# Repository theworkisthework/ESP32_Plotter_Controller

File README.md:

# ESP32 Plotter Controller PCB
 
Released under an MIT licence, no warranty implied or given, use at own risk etc etc.

This is a two axis stepper controller based on the ESP32 and TMC2130 stepper drivers. It is intended to be used with drawing machines and plotters.

Firmware https://github.com/theworkisthework/Grbl_Esp32 (This is a Fork of Grbl_Esp32, if its out of date, you probably only need the config file from this fork). Tested with standard and corexy kinematics and a solenoid/relay for the spindle.

Revision B (aka 'Emerald Dingo') embeds an ESP32 module on the board along with comms and USB C connector. The peripheral connectors are all JST PH2.0 connectors. Also added E-Stop connector (J18).

[Schematic]( https://github.com/theworkisthework/ESP32_Plotter_Controller/blob/main/ESP32_Plotter_Controller_Schematic_RevB1.pdf )

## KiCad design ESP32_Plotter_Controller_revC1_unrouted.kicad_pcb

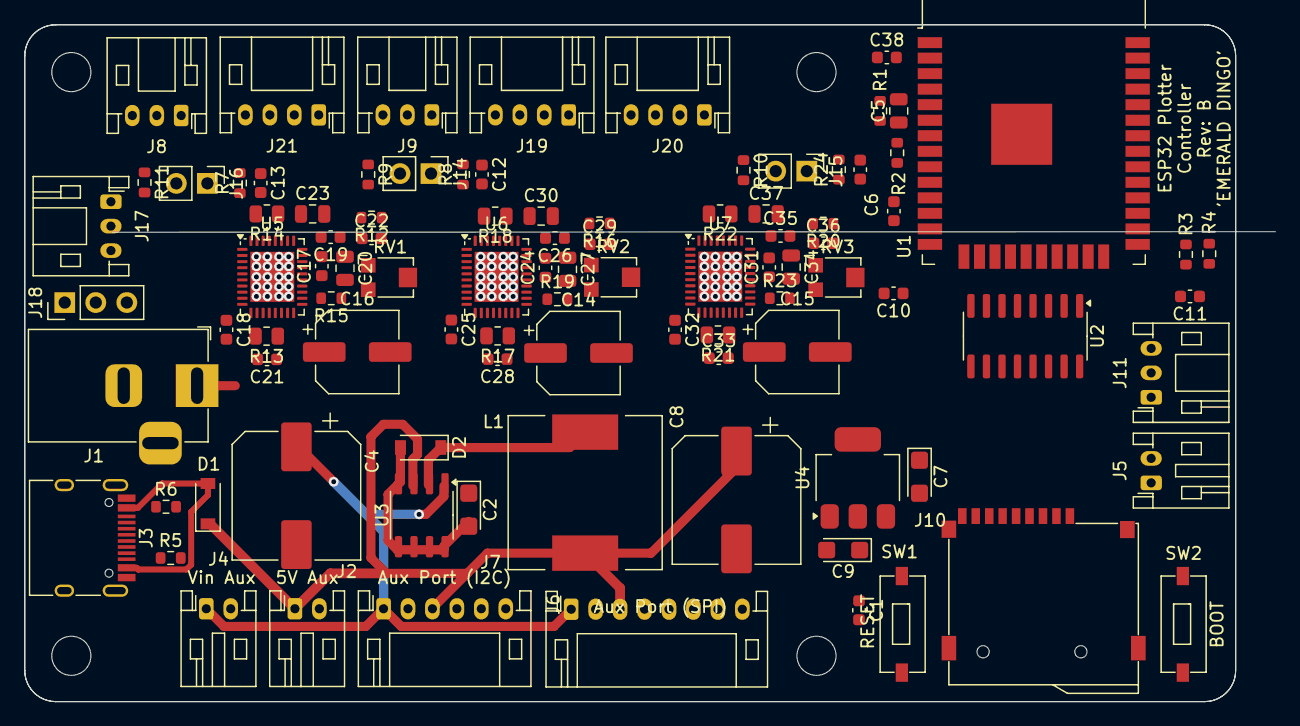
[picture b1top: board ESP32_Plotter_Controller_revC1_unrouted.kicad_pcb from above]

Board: 2 copper layers, 102.3 x 55.4 mm, 96 parts (0 on the bottom side), 83 nets.

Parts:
C1, C3, C6, C10, C11, C12, C13, C38: 100nF; C_0603_1608Metric
C2, C7, C9: 22uF 10v; CP_EIA-3216-18_Kemet-A
C4: 470uF 35v; CP_Elec_10x10
C5: 1uF; C_0805_2012Metric
C8: 220uF 50v; CP_Elec_10x10
C14, C15, C16: 47uF 35V; CP_Elec_6.3x5.7
C17, C24, C31: 22n; C_0603_1608Metric
C18, C19, C21, C25, C26, C28, C32, C33, C35: 100n; C_0603_1608Metric
C20, C27, C34: 4.7u; C_0805_2012Metric
C22, C29, C36: 470n; C_0603_1608Metric
C23, C30, C37: 10u; C_0805_2012Metric
D1, D2: B5819W; D_SOD-123
J1: Power; BarrelJack_Horizontal
J2: 5V Aux; JST_PH_S2B-PH-K_1x02_P2.00mm_Horizontal
J3: USB_C_Receptacle_USB2.0; USB_C_Receptacle_HRO_TYPE-C-31-M-12
J4: Vin Aux; JST_PH_S2B-PH-K_1x02_P2.00mm_Horizontal
J5: E-Stop; JST_PH_S2B-PH-K_1x02_P2.00mm_Horizontal
J6: Aux Port (SPI); JST_PH_S8B-PH-K_1x08_P2.00mm_Horizontal
J7: Aux Port (I2C); JST_PH_S6B-PH-K_1x06_P2.00mm_Horizontal
J8: X Limit Switch; JST_PH_S3B-PH-K_1x03_P2.00mm_Horizontal
J9: Y Limit Switch; JST_PH_S3B-PH-K_1x03_P2.00mm_Horizontal
J10: Micro_SD_Card_TF-01A; HK-TF01A
J11: Z Limit Switch; JST_PH_S3B-PH-K_1x03_P2.00mm_Horizontal
J14: Y Limit; PinHeader_1x02_P2.54mm_Vertical
J15: Z Limit; PinHeader_1x02_P2.54mm_Vertical
J16: X Limit; PinHeader_1x02_P2.54mm_Vertical
J17: Pen Lift; JST_PH_S3B-PH-K_1x03_P2.00mm_Horizontal
J18: Vselect; PinHeader_1x03_P2.54mm_Vertical
J19: Y Motor; JST_PH_S4B-PH-K_1x04_P2.00mm_Horizontal
J20: Z Motor; JST_PH_S4B-PH-K_1x04_P2.00mm_Horizontal
J21: X Motor; JST_PH_S4B-PH-K_1x04_P2.00mm_Horizontal
L1: 68uH; L_12x12mm_H6mm
R1, R3: 5.1k; R_0603_1608Metric
R2, R4, R5, R6, R9, R10, R11: 10k; R_0603_1608Metric
R7, R8, R24: 100; R_0603_1608Metric
R12, R16, R20: 20k; R_0603_1608Metric
R13, R14, R17, R18, R21, R22: 0.11R; R_0805_2012Metric
R15, R19, R23: 2.2R; R_0603_1608Metric
RV1, RV2, RV3: 20k; Potentiometer_Bourns_TC33X_Vertical
SW1: RESET; K2-1107ST
SW2: BOOT; K2-1107ST
U1: ESP32-WROOM-32D; ESP32-WROOM-32
U2: CH340C; SOIC-16_3.9x9.9mm_P1.27mm
U3: XL1509; SO-8_3.9x4.9mm_P1.27mm
U4: AMS1117-3.3; SOT-223-3_TabPin2
U5, U6, U7: TMC2130-LA; QFN-36-1EP_5x6mm_P0.5mm_EP3.6x4.1mm

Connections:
+3.3V: C2.1, C3.1, C6.1, C9.1, C11.1, J6.2, J7.2, J9.1, J10.4 (VDD), J11.1, R2.2, R4.1, R5.1, R6.1, R9.1, R10.1, R11.1, U1.2 (3v3), U2.4 (V3), U2.16 (VCC), U4.2 (VO)
+5V: C7.1, C8.1, D1.1 (K), J2.1, J6.3, J7.3, J18.1, L1.2, U3.3 (Feedback), U4.3 (VI)
/CS_AUX: J6.8, U1.26 (IO4)
/CS_SD: J10.2 (DAT3/CD), U1.29 (IO5)
/CS_X: U1.28 (IO17), U5.2 (~CS_CFG3)
/CS_Y: U1.27 (IO16), U6.2 (~CS_CFG3)
/CS_Z: U1.23 (IO15), U7.2 (~CS_CFG3)
/D+: J3.A6 (D+), J3.B6 (D+), U2.5 (UD+)
/D-: J3.A7 (D-), J3.B7 (D-), U2.6 (UD-)
/EN: C1.2, R2.1, SW1.2, U1.3 (EN)
/ESP32_RX: U1.34 (RXD0), U2.2 (TXD)
/ESP32_TX: U1.35 (TXD0), U2.3 (RXD)
/IO0: C10.1, J5.1, R4.2, SW2.2, U1.25 (IO0)
/MISO: J6.6, J10.7 (DAT0), U1.31 (IO19), U5.5 (SDO_CFG0), U6.5 (SDO_CFG0), U7.5 (SDO_CFG0)
/MOSI: J6.5, J10.3 (CMD), U1.37 (IO23), U5.4 (SDI_CFG1), U6.4 (SDI_CFG1), U7.4 (SDI_CFG1)
/PEN_LIFT: J17.1, U1.12 (IO27)
/SCK: J6.7, J10.5 (CLK), U1.30 (IO18), U5.3 (SCK_CFG2), U6.3 (SCK_CFG2), U7.3 (SCK_CFG2)
/SCL: J7.5, R6.2, U1.36 (IO22)
/SDA: J7.6, R5.2, U1.33 (IO21)
/StepEn: U1.24 (IO2), U5.22 (~DRV_EN_CFG6), U6.22 (~DRV_EN_CFG6), U7.22 (~DRV_EN_CFG6)
/TMC2130_EMBD_1/5VOUT: C20.1, R15.1, U5.25 (5VOUT)
/TMC2130_EMBD_1/A1: J21.2, U5.34 (OA1)
/TMC2130_EMBD_1/A2: J21.1, U5.32 (OA2)
/TMC2130_EMBD_1/B1: J21.3, U5.13 (OB1)
/TMC2130_EMBD_1/B2: J21.4, U5.15 (OB2)
/TMC2130_EMBD_1/DIAG1: J16.2, R11.2, U5.21 (DIAG1)
/TMC2130_EMBD_1/VCC_INT: C22.1, R12.2, R15.2, U5.19 (DCIN_CFG5), U5.26 (VCC)
/TMC2130_EMBD_1/VCP: C19.2, U5.29 (VCP)
/TMC2130_EMBD_1/V_IO: C18.1, U5.8 (VCC_IO)
/TMC2130_EMBD_2/5VOUT: C27.1, R19.1, U6.25 (5VOUT)
/TMC2130_EMBD_2/A1: J19.2, U6.34 (OA1)
/TMC2130_EMBD_2/A2: J19.1, U6.32 (OA2)
/TMC2130_EMBD_2/B1: J19.3, U6.13 (OB1)
/TMC2130_EMBD_2/B2: J19.4, U6.15 (OB2)
/TMC2130_EMBD_2/DIAG1: J14.2, R9.2, U6.21 (DIAG1)
/TMC2130_EMBD_2/VCC_INT: C29.1, R16.2, R19.2, U6.19 (DCIN_CFG5), U6.26 (VCC)
/TMC2130_EMBD_2/VCP: C26.2, U6.29 (VCP)
/TMC2130_EMBD_2/V_IO: C25.1, U6.8 (VCC_IO)
/TMC2130_EMBD_3/5VOUT: C34.1, R23.1, U7.25 (5VOUT)
/TMC2130_EMBD_3/A1: J20.2, U7.34 (OA1)
/TMC2130_EMBD_3/A2: J20.1, U7.32 (OA2)
/TMC2130_EMBD_3/B1: J20.3, U7.13 (OB1)
/TMC2130_EMBD_3/B2: J20.4, U7.15 (OB2)
/TMC2130_EMBD_3/DIAG1: J15.2, R10.2, U7.21 (DIAG1)
/TMC2130_EMBD_3/VCC_INT: C36.1, R20.2, R23.2, U7.19 (DCIN_CFG5), U7.26 (VCC)
/TMC2130_EMBD_3/VCP: C33.2, U7.29 (VCP)
/TMC2130_EMBD_3/V_IO: C32.1, U7.8 (VCC_IO)
/Vin: C4.1, C5.1, C14.1, C15.1, C16.1, C19.1, C21.1, C23.1, C26.1, C28.1, C30.1, C33.1, C35.1, C37.1, J1.1, J4.1, J6.1, J7.1, J18.3, U3.1 (Vin), U5.16 (VS), U5.30 (VSA), U5.31 (VS), U6.16 (VS), U6.30 (VSA), U6.31 (VS), U7.16 (VS), U7.30 (VSA), U7.31 (VS)
/X_Dir: U1.11 (IO26), U5.7 (DIR)
/X_Limit: C13.1, J16.1, R7.1, U1.6 (IO34)
/X_Step: U1.10 (IO25), U5.6 (STEP)
/Y_Dir: U1.9 (IO33), U6.7 (DIR)
/Y_Limit: C12.1, J14.1, R8.1, U1.7 (IO35)
/Y_Step: U1.8 (IO32), U6.6 (STEP)
/Z_Limit: C38.1, J15.1, R24.1, U1.14 (IO12)
/Z_Step: U1.13 (IO14), U7.6 (STEP)
GND: C1.1, C2.2, C3.2, C4.2, C5.2, C6.2, C7.2, C8.2, C9.2, C10.2, C11.2, C12.2, C13.2, C14.2, C15.2, C16.2, C18.2, C20.2, C21.2, C22.2, C23.2, C25.2, C27.2, C28.2, C29.2, C30.2, C32.2, C34.2, C35.2, C36.2, C37.2, C38.2, D2.2 (A), J1.2, J2.2, J3.A1 (GND), J3.A12 (GND), J3.B1 (GND), J3.B12 (GND), J4.2, J5.2, J6.4, J7.4, J8.3, J9.3, J10.6 (VSS), J10.10 (Can), J10.11 (Can), J10.12 (Can), J10.13 (Can), J11.3, J17.3, R1.2, R3.2, R13.2, R14.2, R17.2, R18.2, R21.2, R22.2, RV1.3, RV2.3, RV3.3, SW1.1, SW2.1, U1.1 (GND), U1.15 (GND), U1.38 (GND), U1.39 (GND), U2.1 (GND), U3.4 (~EN), U3.5 (GND), U3.6 (GND), U3.7 (GND), U3.8 (GND), U4.1 (GND), U5.1 (CLK), U5.12 (GNDP), U5.17 (DCO), U5.18 (DCEN_CFG4), U5.24 (GNDA), U5.35 (GNDP), U5.36 (TST_MODE), U5.37 (EP), U6.1 (CLK), U6.12 (GNDP), U6.17 (DCO), U6.18 (DCEN_CFG4), U6.24 (GNDA), U6.35 (GNDP), U6.36 (TST_MODE), U6.37 (EP), U7.1 (CLK), U7.12 (GNDP), U7.17 (DCO), U7.18 (DCEN_CFG4), U7.24 (GNDA), U7.35 (GNDP), U7.36 (TST_MODE), U7.37 (EP)
unnamed: D1.2 (A), J3.A4 (VBUS), J3.A9 (VBUS), J3.B4 (VBUS), J3.B9 (VBUS)
unnamed: D2.1 (K), L1.1, U3.2 (Vout)
unnamed: J3.A5 (CC1), R3.1
unnamed: J3.B5 (CC2), R1.1
unnamed: J8.2, R7.2
unnamed: J9.2, R8.2
unnamed: J11.2, R24.2
unnamed: J17.2, J18.2
unnamed: R12.1, RV1.2
unnamed: R16.1, RV2.2
unnamed: R20.1, RV3.2
unnamed: RV1.1, U5.23 (AIN_IREF)
unnamed: R14.1, U5.33 (BRA)
unnamed: R13.1, U5.14 (BRB)
unnamed: C17.2, U5.28 (CPI)
unnamed: C17.1, U5.27 (CPO)
unnamed: RV2.1, U6.23 (AIN_IREF)
unnamed: R18.1, U6.33 (BRA)
unnamed: R17.1, U6.14 (BRB)
unnamed: C24.2, U6.28 (CPI)
unnamed: C24.1, U6.27 (CPO)
unnamed: RV3.1, U7.23 (AIN_IREF)
unnamed: R22.1, U7.33 (BRA)
unnamed: R21.1, U7.14 (BRB)
unnamed: C31.2, U7.28 (CPI)
unnamed: C31.1, U7.27 (CPO)

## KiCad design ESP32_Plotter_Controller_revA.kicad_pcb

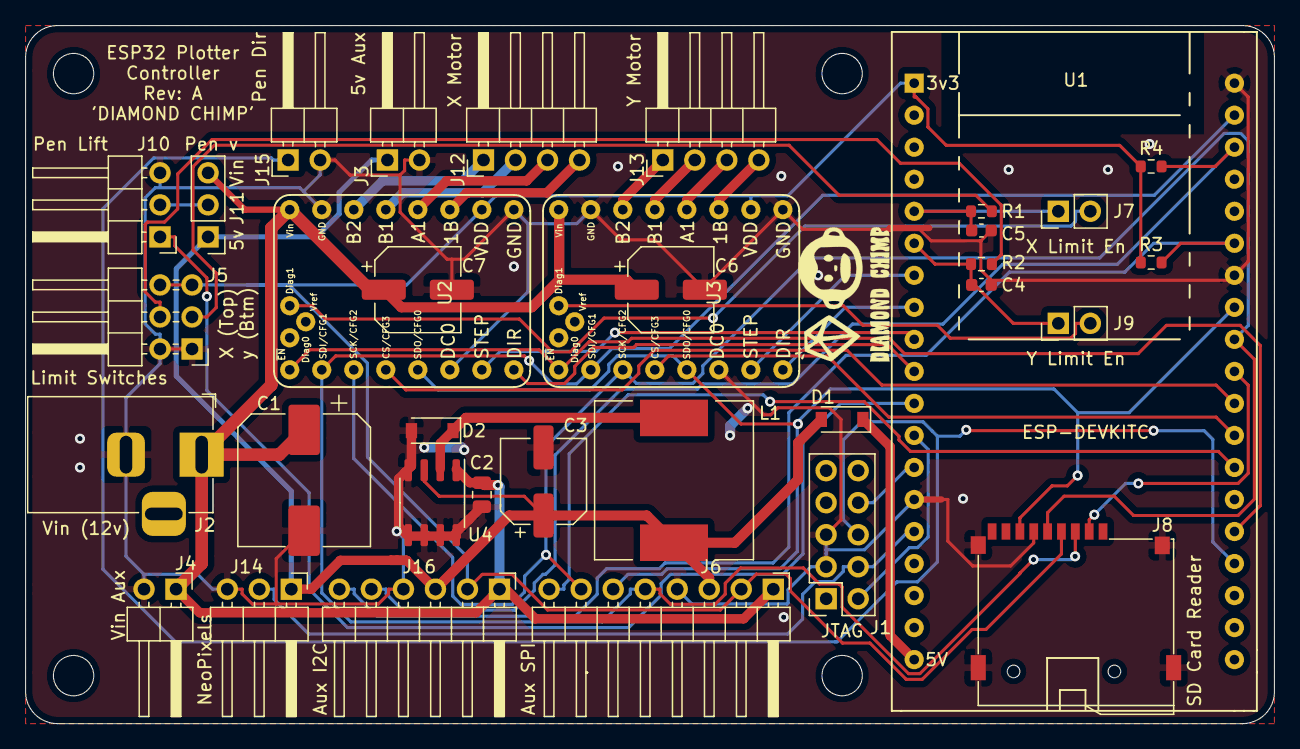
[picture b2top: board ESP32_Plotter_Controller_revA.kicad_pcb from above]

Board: 2 copper layers, 99.1 x 55.4 mm, 38 parts (0 on the bottom side), 40 nets.

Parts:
C1: 470uF 35v; CP_Elec_10x10
C2: 1uF; C_0805_2012Metric
C3: 180uF 35v; CP_Elec_6.3x7.7
C4, C5: 100nF; C_0603_1608Metric
C6, C7: 47uF 35V; CP_Elec_6.3x5.7
D1, D2: B5819W; D_SOD-123
H1, H2, H3, H4: MountingHole_3.2mm_M3
J1: ARM JTAG 10pin; PinSocket_2x05_P2.54mm_Vertical
J2: Power; BarrelJack_Horizontal
J3: 5V Aux; PinHeader_1x02_P2.54mm_Horizontal
J4: Vin Aux; PinHeader_1x02_P2.54mm_Horizontal
J5: Limit Switches; PinHeader_2x03_P2.54mm_Horizontal
J6: Aux Port (SPI); PinHeader_1x08_P2.54mm_Horizontal
J7: X Limit; PinHeader_1x02_P2.54mm_Vertical
J8: Micro_SD_Card_TF-01A; HK-TF01A
J9: Y Limit; PinHeader_1x02_P2.54mm_Vertical
J10: Pen Lift; PinHeader_1x03_P2.54mm_Horizontal
J11: Vselect; PinHeader_1x03_P2.54mm_Vertical
J12: X Motor; PinHeader_1x04_P2.54mm_Horizontal
J13: Y Motor; PinHeader_1x04_P2.54mm_Horizontal
J14: Neo Pixel LEDs; PinHeader_1x03_P2.54mm_Horizontal
J15: Pen Direction; PinHeader_1x02_P2.54mm_Horizontal
J16: Aux Port (I2C); PinHeader_1x06_P2.54mm_Horizontal
L1: 68uH; L_12x12mm_H6mm
R1, R2: 100; R_0603_1608Metric
R3, R4: 10K; R_0603_1608Metric
U1: ESP-DEVKITC; DEVKITC
U2, U3: TMC2130; StepstickTMCv2
U4: XL1509; SO-8_3.9x4.9mm_P1.27mm

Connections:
+3V3: J5.5, J5.6, J6.2, J8.4, J16.2, R3.1, R4.1, U1.1, U2.10, U3.10
+5V: C3.1, D1.2, J3.1, J6.3, J11.1, J14.1, J16.3, L1.2, U4.3
/CS_AUX: J6.8, U1.26
/CS_SD: J8.2, U1.29
/CS_X: U1.28, U2.4
/CS_Y: U1.27, U3.4
/JTAG_TDI: J1.8, U1.13
/JTAG_TMS: J1.2, U1.12
/MISO: J6.6, J8.7, U1.31, U2.5, U3.5
/MOSI: J6.5, J8.3, U1.37, U2.2, U3.2
/NEO_PIXELS_JTAG_TCK: J1.4, J14.2, U1.15
/PEN_DIR_JTAG_TDO: J1.6, J15.1, U1.23
/PEN_LIFT: J10.1, U1.11
/SCK: J6.7, J8.5, U1.30, U2.3, U3.3
/SCL: J16.5, R4.2, U1.36
/SDA: J16.6, R3.2, U1.33
/StepEn: U1.24, U2.1, U3.1
/Vin: C1.1, C2.1, C6.1, C7.1, J2.1, J4.1, J6.1, J11.3, J16.1, U2.16, U3.16, U4.1
/X_Dir: U1.10, U2.8
/X_Limit: C5.1, J7.1, R1.1, U1.5
/X_Step: U1.9, U2.7
/Y_Dir: U1.8, U3.8
/Y_Limit: C4.1, J9.1, R2.1, U1.6
/Y_Step: U1.7, U3.7
GND: C1.2, C2.2, C3.2, C4.2, C5.2, C6.2, C7.2, D2.2, J1.3, J1.5, J2.2, J3.2, J4.2, J5.1, J5.2, J6.4, J8.6, J8.10, J8.11, J8.12, J8.13, J10.3, J14.3, J15.2, J16.4, U1.14, U1.32, U1.38, U2.6, U2.9, U2.15, U3.6, U3.9, U3.15, U4.4, U4.5, U4.6, U4.7, U4.8
unnamed: D1.1, U1.19
unnamed: D2.1, L1.1, U4.2
unnamed: J5.3, R1.2
unnamed: J5.4, R2.2
unnamed: J7.2, U2.18
unnamed: J9.2, U3.18
unnamed: J10.2, J11.2
unnamed: J12.1, U2.14
unnamed: J12.2, U2.13
unnamed: J12.3, U2.12
unnamed: J12.4, U2.11
unnamed: J13.1, U3.14
unnamed: J13.2, U3.13
unnamed: J13.3, U3.12
unnamed: J13.4, U3.11

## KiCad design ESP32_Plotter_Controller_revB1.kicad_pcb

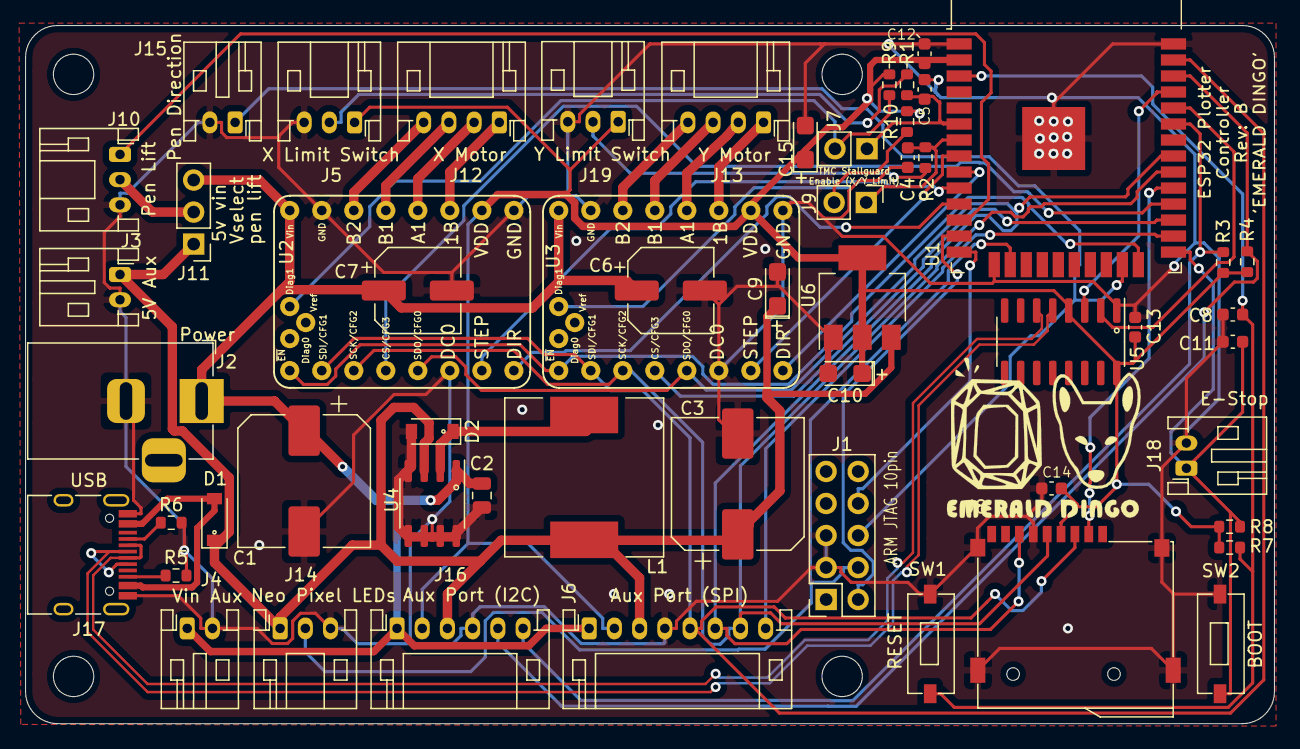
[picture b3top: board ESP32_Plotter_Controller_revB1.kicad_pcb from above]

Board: 2 copper layers, 99.1 x 55.4 mm, 61 parts (1 on the bottom side), 48 nets.

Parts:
C1: 470uF 35v; CP_Elec_10x10
C2: 1uF; C_0805_2012Metric
C3: 220uF 50v; CP_Elec_10x10
C4, C5, C8, C11, C12, C13, C14: 100nF; C_0603_1608Metric
C6, C7: 47uF 35V; CP_Elec_6.3x5.7
C9, C10, C15: 22uF 10v; CP_EIA-3216-18_Kemet-A
D1, D2: B5819W; D_SOD-123
G1: LOGO; emerald_dingo_400
G2: LOGO; emerald_dingo_150
H1, H2, H3, H4: MountingHole_3.2mm_M3
J1: ARM JTAG 10pin; PinSocket_2x05_P2.54mm_Vertical
J2: Power; BarrelJack_Horizontal
J3: 5V Aux; JST_PH_S2B-PH-K_1x02_P2.00mm_Horizontal
J4: Vin Aux; JST_PH_S2B-PH-K_1x02_P2.00mm_Horizontal
J5: X Limit Switch; JST_PH_S3B-PH-K_1x03_P2.00mm_Horizontal
J6: Aux Port (SPI); JST_PH_S8B-PH-K_1x08_P2.00mm_Horizontal
J7: X Limit; PinHeader_1x02_P2.54mm_Vertical
J8: Micro_SD_Card_TF-01A; HK-TF01A
J9: Y Limit; PinHeader_1x02_P2.54mm_Vertical
J10: Pen Lift; JST_PH_S3B-PH-K_1x03_P2.00mm_Horizontal
J11: Vselect; PinHeader_1x03_P2.54mm_Vertical
J12: X Motor; JST_PH_S4B-PH-K_1x04_P2.00mm_Horizontal
J13: Y Motor; JST_PH_S4B-PH-K_1x04_P2.00mm_Horizontal
J14: Neo Pixel LEDs; JST_PH_S3B-PH-K_1x03_P2.00mm_Horizontal
J15: Pen Direction; JST_PH_S2B-PH-K_1x02_P2.00mm_Horizontal
J16: Aux Port (I2C); JST_PH_S6B-PH-K_1x06_P2.00mm_Horizontal
J17: USB_C_Receptacle_USB2.0; USB_C_Receptacle_HRO_TYPE-C-31-M-12
J18: E-Stop; JST_PH_S2B-PH-K_1x02_P2.00mm_Horizontal
J19: Y Limit Switch; JST_PH_S3B-PH-K_1x03_P2.00mm_Horizontal
L1: 68uH; L_12x12mm_H6mm
R1, R2: 100; R_0603_1608Metric
R3, R4, R7, R8, R9, R10: 10k; R_0603_1608Metric
R5, R6: 5.1k; R_0603_1608Metric
SW1: RESET; K2-1107ST
SW2: BOOT; K2-1107ST
U1: ESP32-WROOM-32D; ESP32-WROOM-32
U2, U3: TMC2130; StepstickTMCv2
U4: XL1509; SO-8_3.9x4.9mm_P1.27mm
U5: CH340C; SOIC-16_3.9x9.9mm_P1.27mm
U6: AMS1117-3.3; SOT-223-3_TabPin2

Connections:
+3V3: C10.1, C12.1, C13.1, C14.1, C15.1, J5.1, J6.2, J8.4, J16.2, J19.1, R3.1, R4.1, R7.2, R8.1, R9.1, R10.1, U1.2, U2.10, U3.10, U5.4, U5.16, U6.2
+5V: C3.1, C9.1, D1.1, J3.1, J6.3, J11.1, J14.1, J16.3, L1.2, U4.3, U6.3
/CS_AUX: J6.8, U1.26
/CS_SD: J8.2, U1.29
/CS_X: U1.28, U2.4
/CS_Y: U1.27, U3.4
/D+: J17.A6, J17.B6, U5.5
/D-: J17.A7, J17.B7, U5.6
/EN: C8.2, R7.1, SW1.2, U1.3
/ESP32_RX: U1.34, U5.2
/ESP32_TX: U1.35, U5.3
/IO0: C11.1, J18.1, R8.2, SW2.2, U1.25
/JTAG_TDI: J1.8, U1.14
/JTAG_TMS: J1.2, U1.13
/MISO: J6.6, J8.7, U1.31, U2.5, U3.5
/MOSI: J6.5, J8.3, U1.37, U2.2, U3.2
/NEO_PIXELS_JTAG_TCK: J1.4, J14.2, U1.16
/PEN_DIR_JTAG_TDO: J1.6, J15.1, U1.23
/PEN_LIFT: J10.1, U1.12
/SCK: J6.7, J8.5, U1.30, U2.3, U3.3
/SCL: J16.5, R4.2, U1.36
/SDA: J16.6, R3.2, U1.33
/StepEn: U1.24, U2.1, U3.1
/Vin: C1.1, C2.1, C6.1, C7.1, J2.1, J4.1, J6.1, J11.3, J16.1, U2.16, U3.16, U4.1
/X_Dir: U1.11, U2.8
/X_Limit: C5.1, J7.1, R1.1, U1.6
/X_Step: U1.10, U2.7
/Y_Dir: U1.9, U3.8
/Y_Limit: C4.1, J9.1, R2.1, U1.7
/Y_Step: U1.8, U3.7
GND: C1.2, C2.2, C3.2, C4.2, C5.2, C6.2, C7.2, C8.1, C9.2, C10.2, C11.2, C12.2, C13.2, C14.2, C15.2, D2.2, J1.3, J1.5, J2.2, J3.2, J4.2, J5.3, J6.4, J8.6, J8.10, J8.11, J8.12, J8.13, J10.3, J14.3, J15.2, J16.4, J17.A1, J17.A12, J17.B1, J17.B12, J18.2, J19.3, R5.2, R6.2, SW1.1, SW2.1, U1.1, U1.15, U1.38, U1.39, U2.6, U2.9, U2.15, U3.6, U3.9, U3.15, U4.4, U4.5, U4.6, U4.7, U4.8, U5.1, U6.1
unnamed: D1.2, J17.A4, J17.A9, J17.B4, J17.B9
unnamed: D2.1, L1.1, U4.2
unnamed: J5.2, R1.2
unnamed: J7.2, R9.2, U2.18
unnamed: J9.2, R10.2, U3.18
unnamed: J10.2, J11.2
unnamed: J12.1, U2.11
unnamed: J12.2, U2.12
unnamed: J12.3, U2.13
unnamed: J12.4, U2.14
unnamed: J13.1, U3.11
unnamed: J13.2, U3.12
unnamed: J13.3, U3.13
unnamed: J13.4, U3.14
unnamed: J17.A5, R6.1
unnamed: J17.B5, R5.1
unnamed: J19.2, R2.2

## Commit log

2022-06-03 Update repo links
2022-06-03 Update repo links in pinmap
2022-06-03 Update gerber files
2022-06-12 Fix solenoid pin order on pinmap
    GND and En pins were swapped on diagram. Fixed in this version
2024-12-06 Fix J19 pins swapped on pin map
2025-06-03 Add TMC2130-LA on-board drivers
2025-06-03 Might as well add a z motor stepper driver at this stage
2025-06-03 Assign JTAG pins to Z stepper driver. Remove JTAG, Pen Direction and Neo Pixel ports
2025-06-06 All components placed - first pass
